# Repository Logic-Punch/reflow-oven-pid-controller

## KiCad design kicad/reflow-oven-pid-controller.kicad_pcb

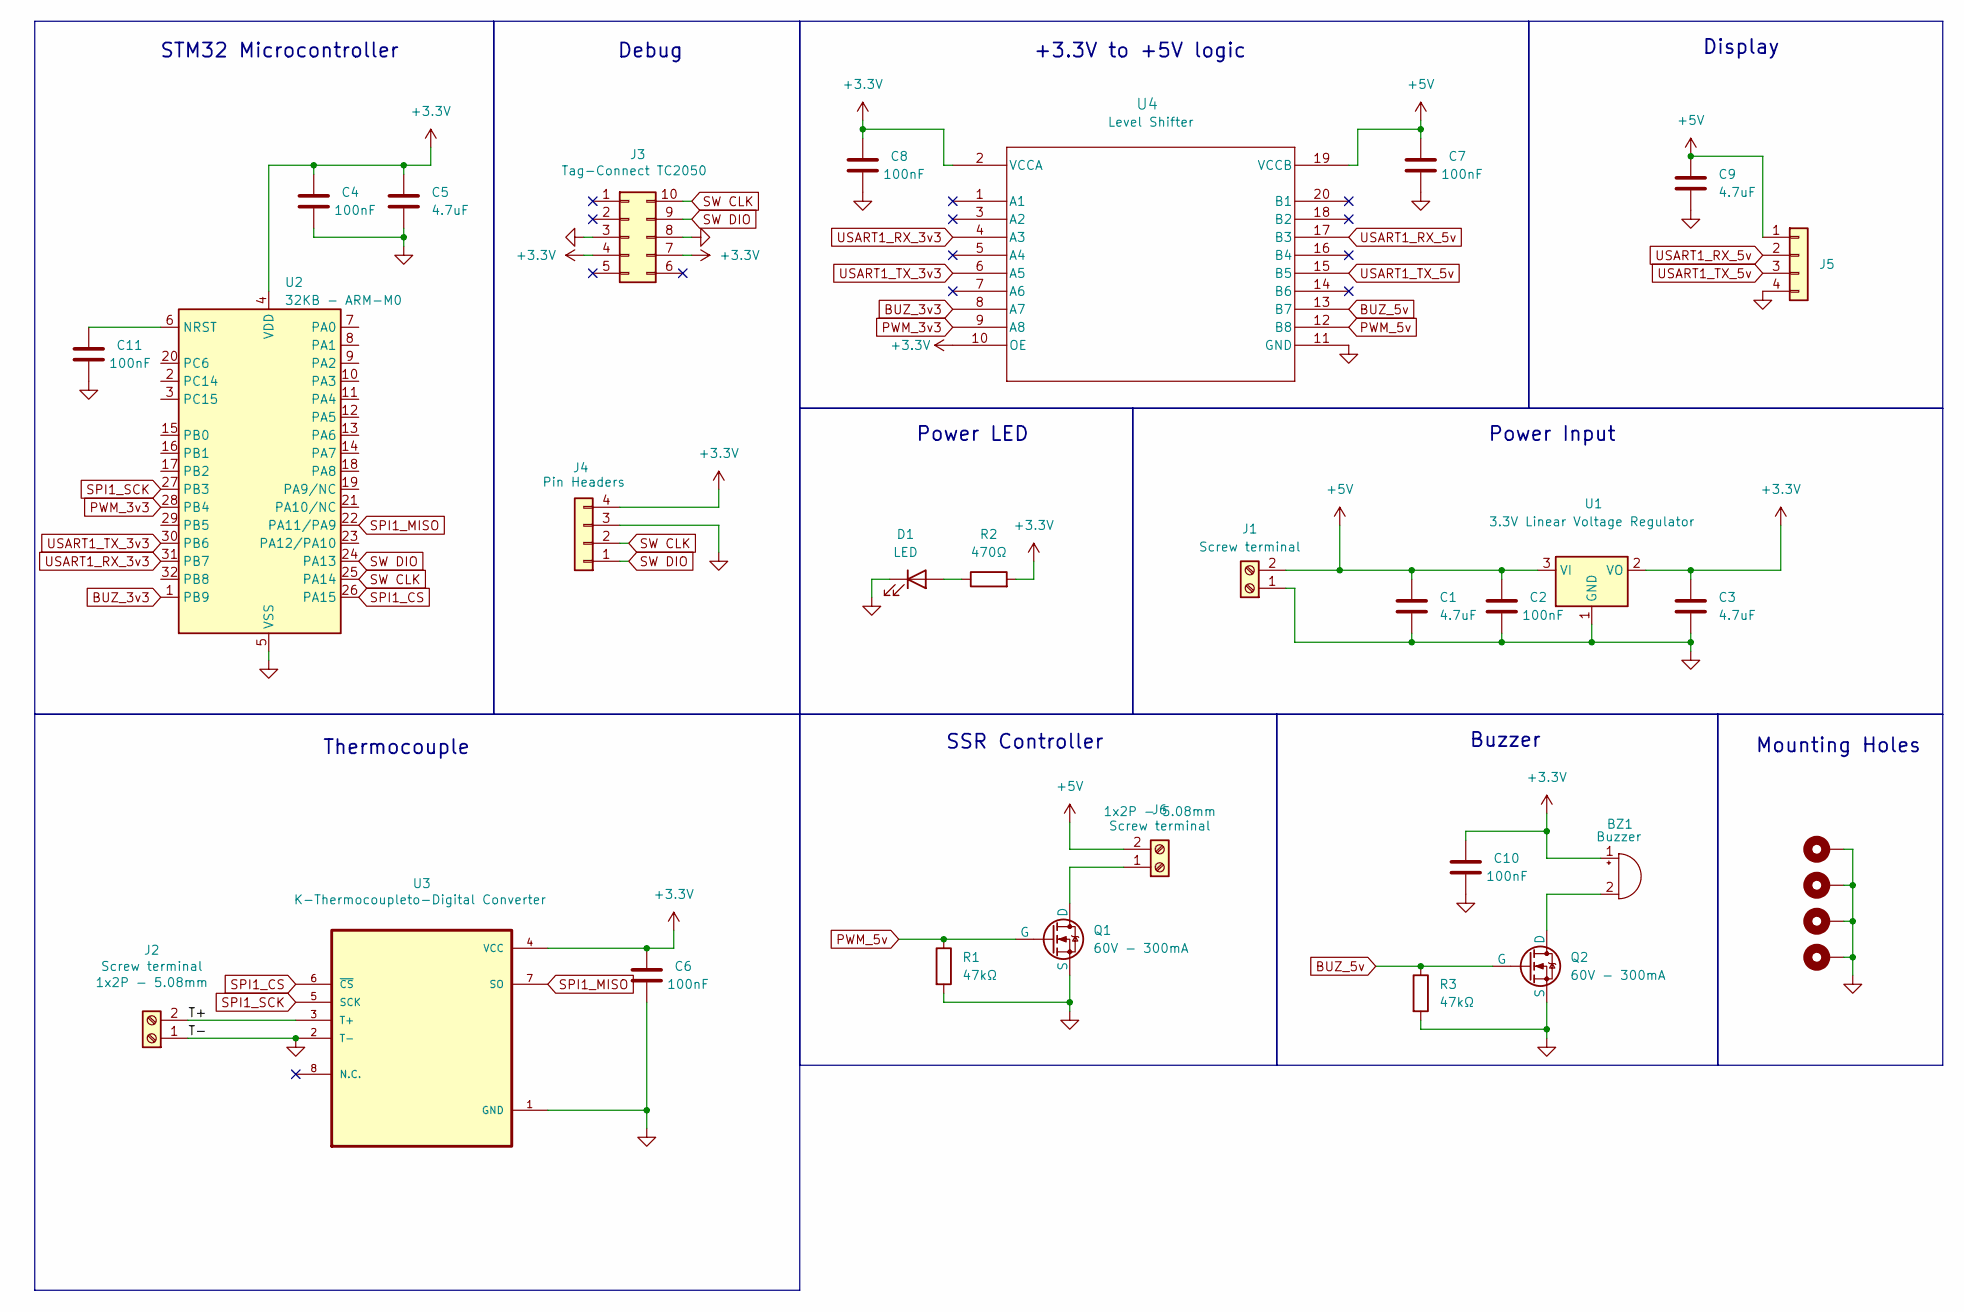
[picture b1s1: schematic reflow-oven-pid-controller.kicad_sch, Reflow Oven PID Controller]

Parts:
BZ1: 3kHz - 85dB; BUZ-TH_BD9.0-P5.00-D0.6-FD; Part Number HNB09A03; LCSC C96102
C1, C3, C5, C9: 4.7uF; C_0805_2012Metric; Part Number EMK212B7475KG-T; LCSC C92762
C2, C4, C6, C7, C8, C10, C11: 100nF; C_0805_2012Metric; Part Number C0805B104K500NT; LCSC C476766
D1: LED; LED_0805_2012Metric; Part Number NCD0805B2; LCSC C84259
H1, H2, H3, H4: MountingHole_Pad; MountingHole_3.2mm_M3_Pad_Via
J1, J2, J6: 1x2P - 5.08mm; CONN-TH_2P-P5.00_WJ500V-5.08-2P; Part Number WJ500V-5.08-2P; LCSC C8465
J3: Tag-Connect_TC2050-IDC-FP_2x05_P1.27mm_Vertical
J4: 1x4P - 2.54mm; PinHeader_1x04_P2.54mm_Vertical; Part Number PZ254V-11-04P; LCSC C2691448
J5: 1x4P - Right-Angle; CONN-TH_4P-P2.50_ZX-XH2.54-4PWZ; Part Number ZX-XH2.54-4PWZ; LCSC C7429643
Q1, Q2: 60V - 300mA; SOT-23; Part Number 2N7002K; LCSC C3008053
R1, R3: 47kΩ; R_0805_2012Metric; Part Number 0805W8F4702T5E; LCSC C17713
R2: 470Ω; R_0805_2012Metric; Part Number 0805W8F4700T5E; LCSC C17710
U1: 3.3v - 500mA; SOT-223-3_TabPin2; Part Number AMS1117-3.3; LCSC C347222
U2: 32KB - ARM-M0; LQFP-32_7x7mm_P0.8mm; Part Number STM32G030K6T6; LCSC C529331
U3: 1 Channel; SOIC-8_3.9x4.9mm_P1.27mm; Part Number MAX6675ISA+T; LCSC C16030
U4: 8 Channel - Bi-Directional; TSSOP-20_4.4x6.5mm_P0.65mm; Part Number TXB0108PWR; LCSC C53406

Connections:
+3.3V: BZ1.1 (+), C3.1, C4.1, C5.1, C6.1, C8.1, C10.1, J3.4, J3.7, J4.4, R2.2, U1.2 (VO), U2.4 (VDD), U3.4 (VCC), U4.2 (VCCA), U4.10 (OE)
+5V: C1.1, C2.1, C7.1, C9.1, J1.2, J5.1, J6.2, U1.3 (VI), U4.19 (VCCB)
/T+: J2.2, U3.3 (T+)
BUZ_3v3: U2.1 (PB9), U4.8 (A7)
BUZ_5v: Q2.2 (G), R3.1, U4.13 (B7)
GND: C1.2, C2.2, C3.2, C4.2, C5.2, C6.2, C7.2, C8.2, C9.2, C10.2, C11.2, D1.1 (K), H1.1, H2.1, H3.1, H4.1, J1.1, J2.1, J3.3, J3.8, J4.3, J5.4, Q1.3 (S), Q2.3 (S), R1.2, R3.2, U1.1 (GND), U2.5 (VSS), U3.1 (GND), U3.2 (T-), U4.11 (GND)
unnamed: BZ1.2 (-), Q2.1 (D)
unnamed: D1.2 (A), R2.1
unnamed: J6.1, Q1.1 (D)
unnamed: C11.1, U2.6 (NRST)
PWM_3v3: U2.28 (PB4), U4.9 (A8)
PWM_5v: Q1.2 (G), R1.1, U4.12 (B8)
SPI1_CS: U2.26 (PA15), U3.6 (~CS)
SPI1_MISO: U2.22 (PA11/PA9), U3.7 (SO)
SPI1_SCK: U2.27 (PB3), U3.5 (SCK)
SW CLK: J3.10, J4.2, U2.25 (PA14)
SW DIO: J3.9, J4.1, U2.24 (PA13)
USART1_RX_3v3: U2.31 (PB7), U4.4 (A3)
USART1_RX_5v: J5.2, U4.17 (B3)
USART1_TX_3v3: U2.30 (PB6), U4.6 (A5)
USART1_TX_5v: J5.3, U4.15 (B5)

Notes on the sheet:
Thermocouple
Buzzer
STM32 Microcontroller
+3.3V to +5V logic
SSR Controller
Mounting Holes
Display
Debug
Power Input
Power LED

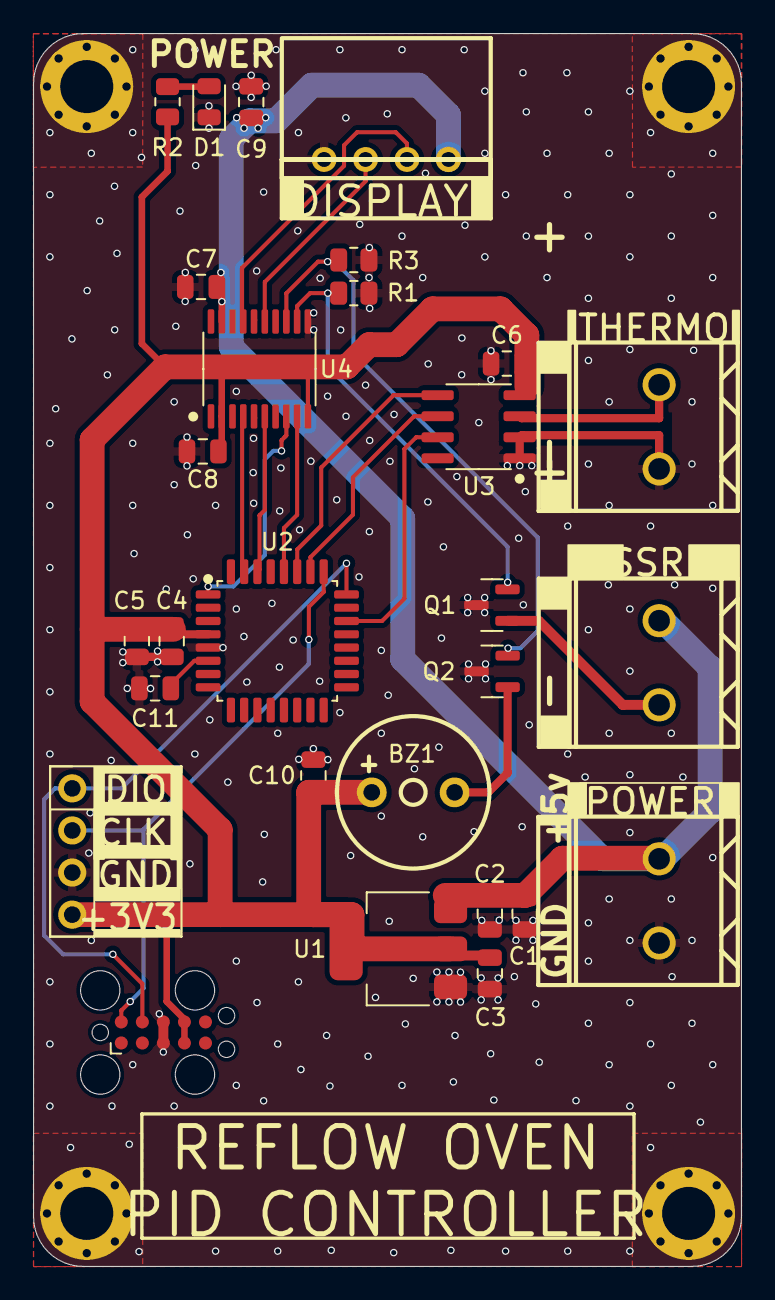
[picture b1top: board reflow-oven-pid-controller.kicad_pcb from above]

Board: 4 copper layers, 42.7 x 74.4 mm, 32 parts (0 on the bottom side), 21 nets.

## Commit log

2024-06-21 hardware init
2024-06-30 nextion init
2024-07-12 Hardware updates
    * Made adjustments for easier hand solder, More spacing and added thermal reliefs
    * Changed LDO component as selected wrong footprint for old one.
    * Moved power led to top of board
    * Changed power led resistor to hopefully make led less bright
    * Added cap to MCU NRST as this was somehow forgotten rendering the MCU none working.
    * Adjusted screw terminal footprints slightly as board overhand was too much.
